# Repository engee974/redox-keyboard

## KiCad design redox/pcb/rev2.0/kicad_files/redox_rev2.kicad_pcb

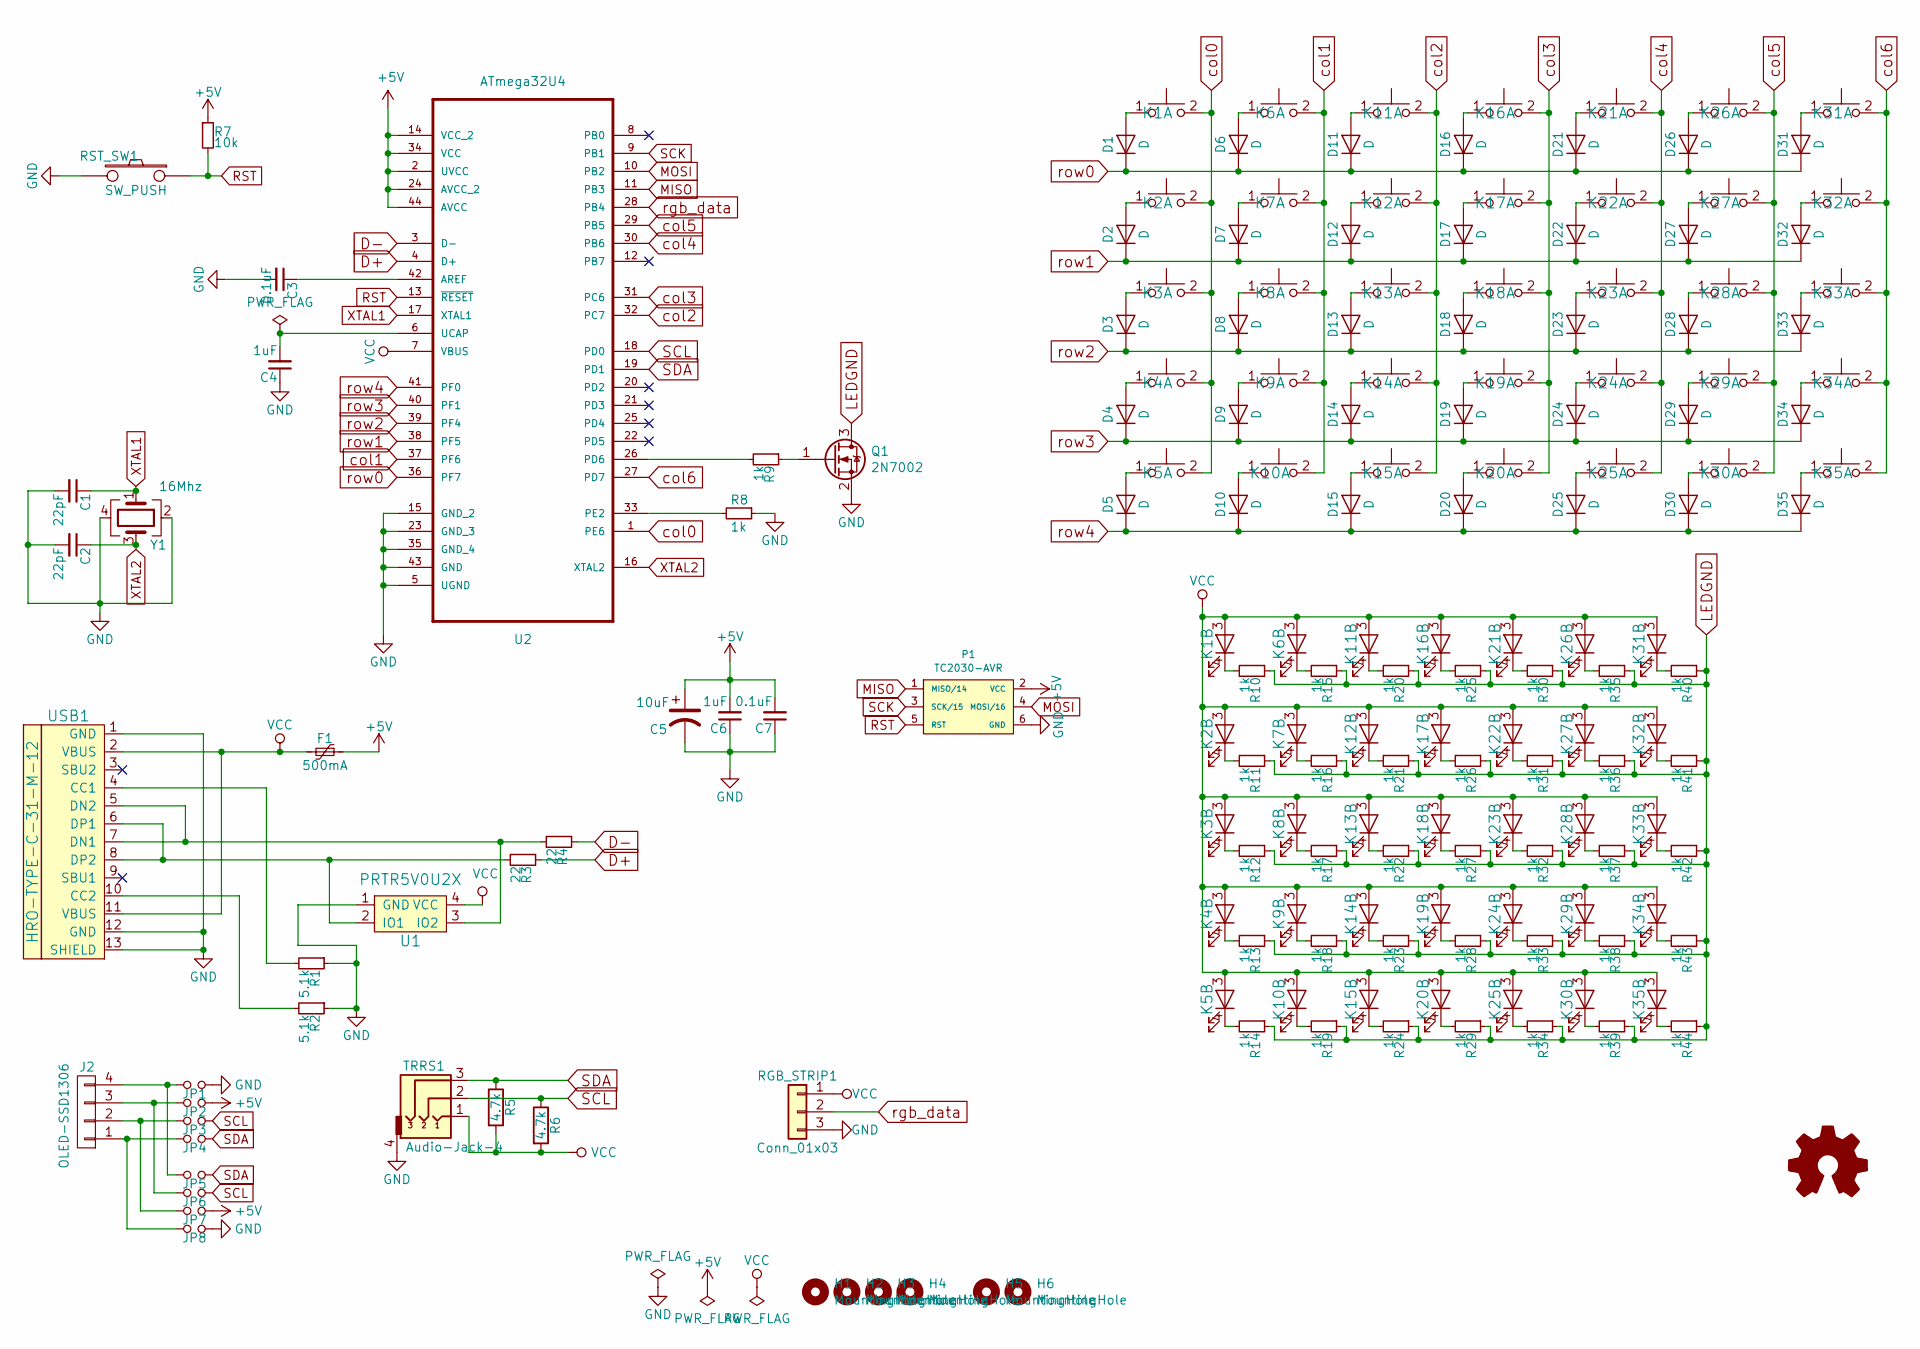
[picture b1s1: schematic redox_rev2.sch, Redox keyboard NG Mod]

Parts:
C1, C2: 22pF; C_0603
C3, C7: 0.1uF; C_0603
C4, C6: 1uF; C_0603
C5: 10uF; CP_EIA-3216-12_Kemet-S_Pad1.58x1.35mm_HandSolder
D1, D2, D3, D4, D5, D6, D7, D8, D9, D10, D11, D12, D13, D14, D15, D16, D17, D18, D19, D20, D21, D22, D23, D24, D25, D26, D27, D28, D29, D30, D31, D32, D33, D34, D35: D; D_0805_dualsided
F1: 500mA; Fuse_1206_3216Metric_Pad1.42x1.75mm_HandSolder
H1, H2, H3, H4: MountingHole; HOLE_M3
H5, H6: MountingHole; M2_HOLE_PCB
J2: OLED-SSD1306; OLED_4Pin
JP1, JP2, JP3, JP4, JP5, JP6, JP7, JP8: Jumper_NO_Small; Jumper
K1, K2, K3, K4, K25, K30, K32, K35: KEYSW; Mx_Alps_125-dualside_with_LED
K5, K6, K7, K8, K9, K10, K11, K12, K13, K14, K15, K16, K17, K18, K19, K20, K21, K22, K23, K24, K26, K27, K28, K29, K31, K33, K34: KEYSW; Mx_Alps_100-dualside_with_LED
P1: TC2030-AVR; PinHeader_2x03_P2.54mm_Vertical
Q1: 2N7002; SOT-23
R1, R2: 5.1k; R_0603
R3, R4: 22; R_0603
R5, R6: 4.7k; Resistor-Compact
R7: 10k; R_0603
R8, R9: 1k; R_0603
R10, R11, R12, R13, R14, R15, R16, R17, R18, R19, R20, R21, R22, R23, R24, R25, R26, R27, R28, R29, R30, R31, R32, R33, R34, R35, R36, R37, R38, R39, R40, R41, R42, R43, R44: 1k; R_0805_dualsided
RGB_STRIP1: Conn_01x03; PinHeader_1x03_P2.54mm_Vertical
RST_SW1: SW_PUSH; TACT_SWITCH_TVBP06
TRRS1: Audio-Jack-4; TRRS-PJ-320A-dual
U1: PRTR5V0U2X; SOT143B
U2: ATmega32U4; QFN-44-1EP_7x7mm_P0.5mm_EP5.2x5.2mm_ThermalVias
USB1: HRO-TYPE-C-31-M-12; HRO-TYPE-C-31-M-12-Assembly_dualsided
Y1: 16Mhz; Crystal_SMD_3225-4Pin_3.2x2.5mm

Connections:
+5V: C5.1, C6.2, C7.2, F1.1, JP2.2, JP7.2, P1.2 (VCC), R7.1, U2.2 (UVCC), U2.14 (VCC_2), U2.24 (AVCC_2), U2.34 (VCC), U2.44 (AVCC)
D+: R3.1, U2.4 (D+)
D-: R4.1, U2.3 (D-)
GND: C1.2, C2.2, C3.2, C4.1, C5.2, C6.1, C7.1, JP1.2, JP8.2, P1.6 (GND), Q1.2 (S), R1.1, R2.1, R8.1, RGB_STRIP1.3, RST_SW1.2, TRRS1.4, U1.1 (GND), U2.5 (UGND), U2.15 (GND_2), U2.23 (GND_3), U2.35 (GND_4), U2.43 (GND), USB1.1 (GND), USB1.12 (GND), USB1.13 (SHIELD), Y1.2, Y1.4
LEDGND: Q1.3 (D), R10.1, R11.1, R12.1, R13.1, R14.1, R15.1, R16.1, R17.1, R18.1, R19.1, R20.1, R21.1, R22.1, R23.1, R24.1, R25.1, R26.1, R27.1, R28.1, R29.1, R30.1, R31.1, R32.1, R33.1, R34.1, R35.1, R36.1, R37.1, R38.1, R39.1, R40.1, R41.1, R42.1, R43.1, R44.1
MISO: P1.1 (MISO/14), U2.11 (PB3)
MOSI: P1.4 (MOSI/16), U2.10 (PB2)
unnamed: C3.1, U2.42 (AREF)
unnamed: C4.2, U2.6 (UCAP)
unnamed: D1.2 (A), K1.1
unnamed: D2.2 (A), K2.1
unnamed: D3.2 (A), K3.1
unnamed: D4.2 (A), K4.1
unnamed: D5.2 (A), K5.1
unnamed: D6.2 (A), K6.1
unnamed: D7.2 (A), K7.1
unnamed: D8.2 (A), K8.1
unnamed: D9.2 (A), K9.1
unnamed: D10.2 (A), K10.1
unnamed: D11.2 (A), K11.1
unnamed: D12.2 (A), K12.1
unnamed: D13.2 (A), K13.1
unnamed: D14.2 (A), K14.1
unnamed: D15.2 (A), K15.1
unnamed: D16.2 (A), K16.1
unnamed: D17.2 (A), K17.1
unnamed: D18.2 (A), K18.1
unnamed: D19.2 (A), K19.1
unnamed: D20.2 (A), K20.1
unnamed: D21.2 (A), K21.1
unnamed: D22.2 (A), K22.1
unnamed: D23.2 (A), K23.1
unnamed: D24.2 (A), K24.1
unnamed: D25.2 (A), K25.1
unnamed: D26.2 (A), K26.1
unnamed: D27.2 (A), K27.1
unnamed: D28.2 (A), K28.1
unnamed: D29.2 (A), K29.1
unnamed: D30.2 (A), K30.1
unnamed: D31.2 (A), K31.1
unnamed: D32.2 (A), K32.1
unnamed: D33.2 (A), K33.1
unnamed: D34.2 (A), K34.1
unnamed: D35.2 (A), K35.1
unnamed: J2.1, JP4.1, JP8.1
unnamed: J2.2, JP3.1, JP7.1
unnamed: J2.3, JP2.1, JP6.1
unnamed: J2.4, JP1.1, JP5.1
unnamed: K1.4, R10.2
unnamed: K2.4, R11.2
unnamed: K3.4, R12.2
unnamed: K4.4, R13.2
unnamed: K5.4, R14.2
unnamed: K6.4, R15.2
unnamed: K7.4, R16.2
unnamed: K8.4, R17.2
unnamed: K9.4, R18.2
unnamed: K10.4, R19.2
unnamed: K11.4, R20.2
unnamed: K12.4, R21.2
unnamed: K13.4, R22.2
unnamed: K14.4, R23.2
unnamed: K15.4, R24.2
unnamed: K16.4, R25.2
unnamed: K17.4, R26.2
unnamed: K18.4, R27.2
unnamed: K19.4, R28.2
unnamed: K20.4, R29.2
unnamed: K21.4, R30.2
unnamed: K22.4, R31.2
unnamed: K23.4, R32.2
unnamed: K24.4, R33.2
unnamed: K25.4, R34.2
unnamed: K26.4, R35.2
unnamed: K27.4, R36.2
unnamed: K28.4, R37.2
unnamed: K29.4, R38.2
unnamed: K30.4, R39.2
unnamed: K31.4, R40.2
unnamed: K32.4, R41.2
unnamed: K33.4, R42.2
unnamed: K34.4, R43.2
unnamed: K35.4, R44.2
unnamed: Q1.1 (G), R9.1
unnamed: R1.2, USB1.4 (CC1)
unnamed: R2.2, USB1.10 (CC2)
unnamed: R3.2, U1.2 (IO1), USB1.6 (DP1), USB1.8 (DP2)
unnamed: R4.2, U1.3 (IO2), USB1.5 (DN2), USB1.7 (DN1)
unnamed: R8.2, U2.33 (PE2)
unnamed: R9.2, U2.26 (PD6)
RST: P1.5 (RST), R7.2, RST_SW1.1, U2.13 (~RESET)
SCK: P1.3 (SCK/15), U2.9 (PB1)
SCL: JP3.2, JP6.2, R6.1, TRRS1.2, U2.18 (PD0)
SDA: JP4.2, JP5.2, R5.1, TRRS1.3, U2.19 (PD1)
VCC: F1.2, K1.3, K2.3, K3.3, K4.3, K5.3, K6.3, K7.3, K8.3, K9.3, K10.3, K11.3, K12.3, K13.3, K14.3, K15.3, K16.3, K17.3, K18.3, K19.3, K20.3, K21.3, K22.3, K23.3, K24.3, K25.3, K26.3, K27.3, K28.3, K29.3, K30.3, K31.3, K32.3, K33.3, K34.3, K35.3, R5.2, R6.2, RGB_STRIP1.1, TRRS1.1, U1.4 (VCC), U2.7 (VBUS), USB1.2 (VBUS), USB1.11 (VBUS)
XTAL1: C1.1, U2.17 (XTAL1), Y1.1
XTAL2: C2.1, U2.16 (XTAL2), Y1.3
col0: K1.2, K2.2, K3.2, K4.2, K5.2, U2.1 (PE6)
col1: K6.2, K7.2, K8.2, K9.2, K10.2, U2.37 (PF6)
col2: K11.2, K12.2, K13.2, K14.2, K15.2, U2.32 (PC7)
col3: K16.2, K17.2, K18.2, K19.2, K20.2, U2.31 (PC6)
col4: K21.2, K22.2, K23.2, K24.2, K25.2, U2.30 (PB6)
col5: K26.2, K27.2, K28.2, K29.2, K30.2, U2.29 (PB5)
col6: K31.2, K32.2, K33.2, K34.2, K35.2, U2.27 (PD7)
rgb_data: RGB_STRIP1.2, U2.28 (PB4)
row0: D1.1 (K), D6.1 (K), D11.1 (K), D16.1 (K), D21.1 (K), D26.1 (K), D31.1 (K), U2.36 (PF7)
row1: D2.1 (K), D7.1 (K), D12.1 (K), D17.1 (K), D22.1 (K), D27.1 (K), D32.1 (K), U2.38 (PF5)
row2: D3.1 (K), D8.1 (K), D13.1 (K), D18.1 (K), D23.1 (K), D28.1 (K), D33.1 (K), U2.39 (PF4)
row3: D4.1 (K), D9.1 (K), D14.1 (K), D19.1 (K), D24.1 (K), D29.1 (K), D34.1 (K), U2.40 (PF1)
row4: D5.1 (K), D10.1 (K), D15.1 (K), D20.1 (K), D25.1 (K), D30.1 (K), D35.1 (K), U2.41 (PF0)

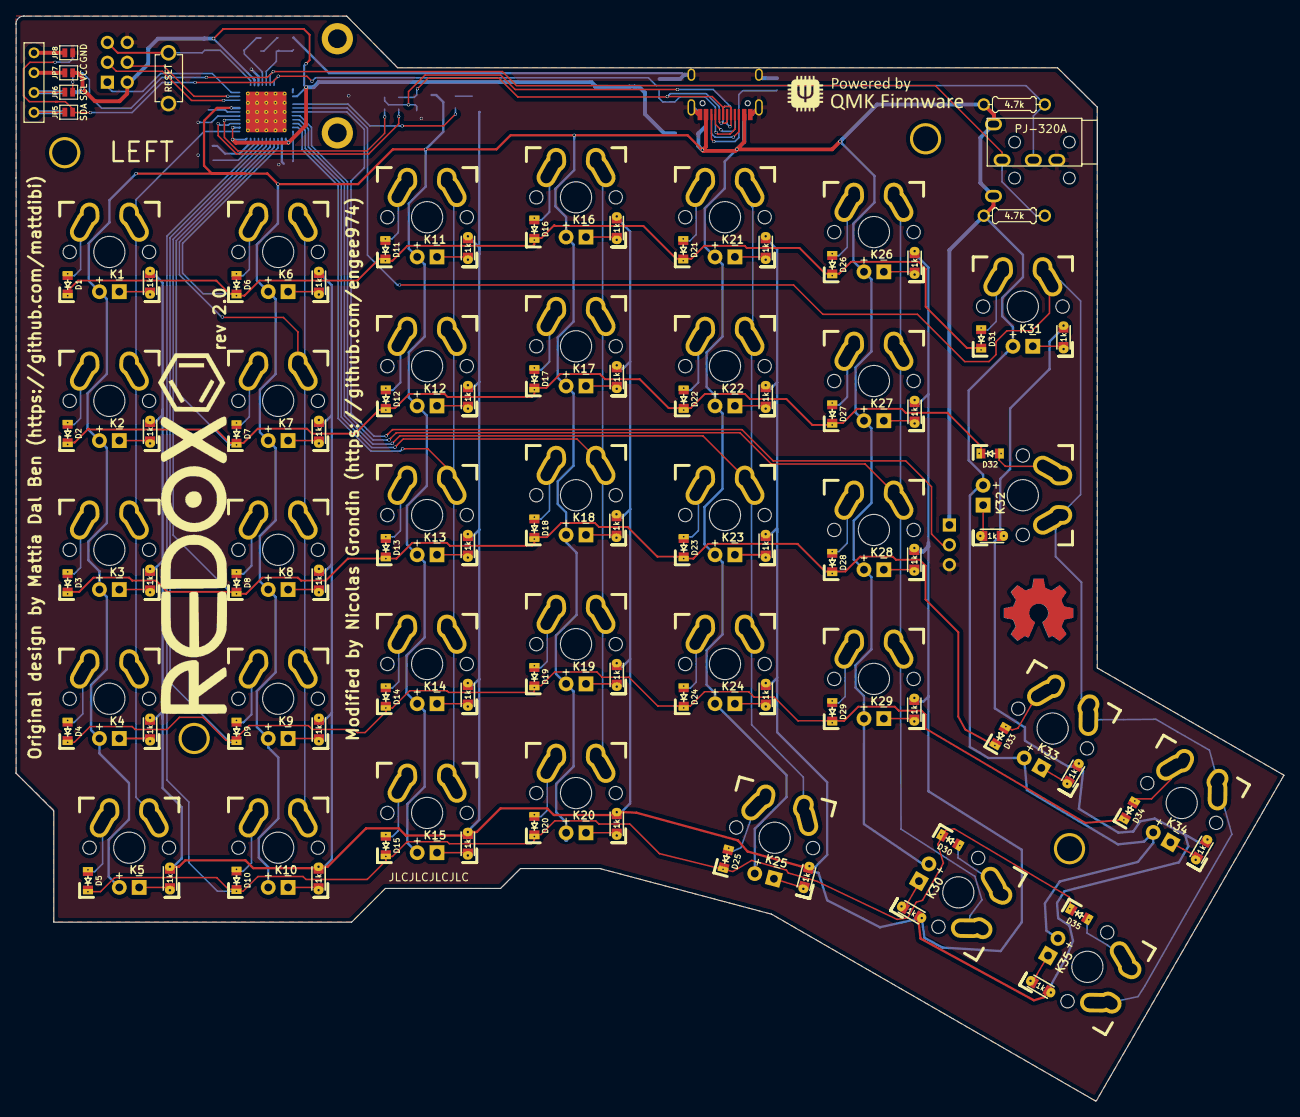
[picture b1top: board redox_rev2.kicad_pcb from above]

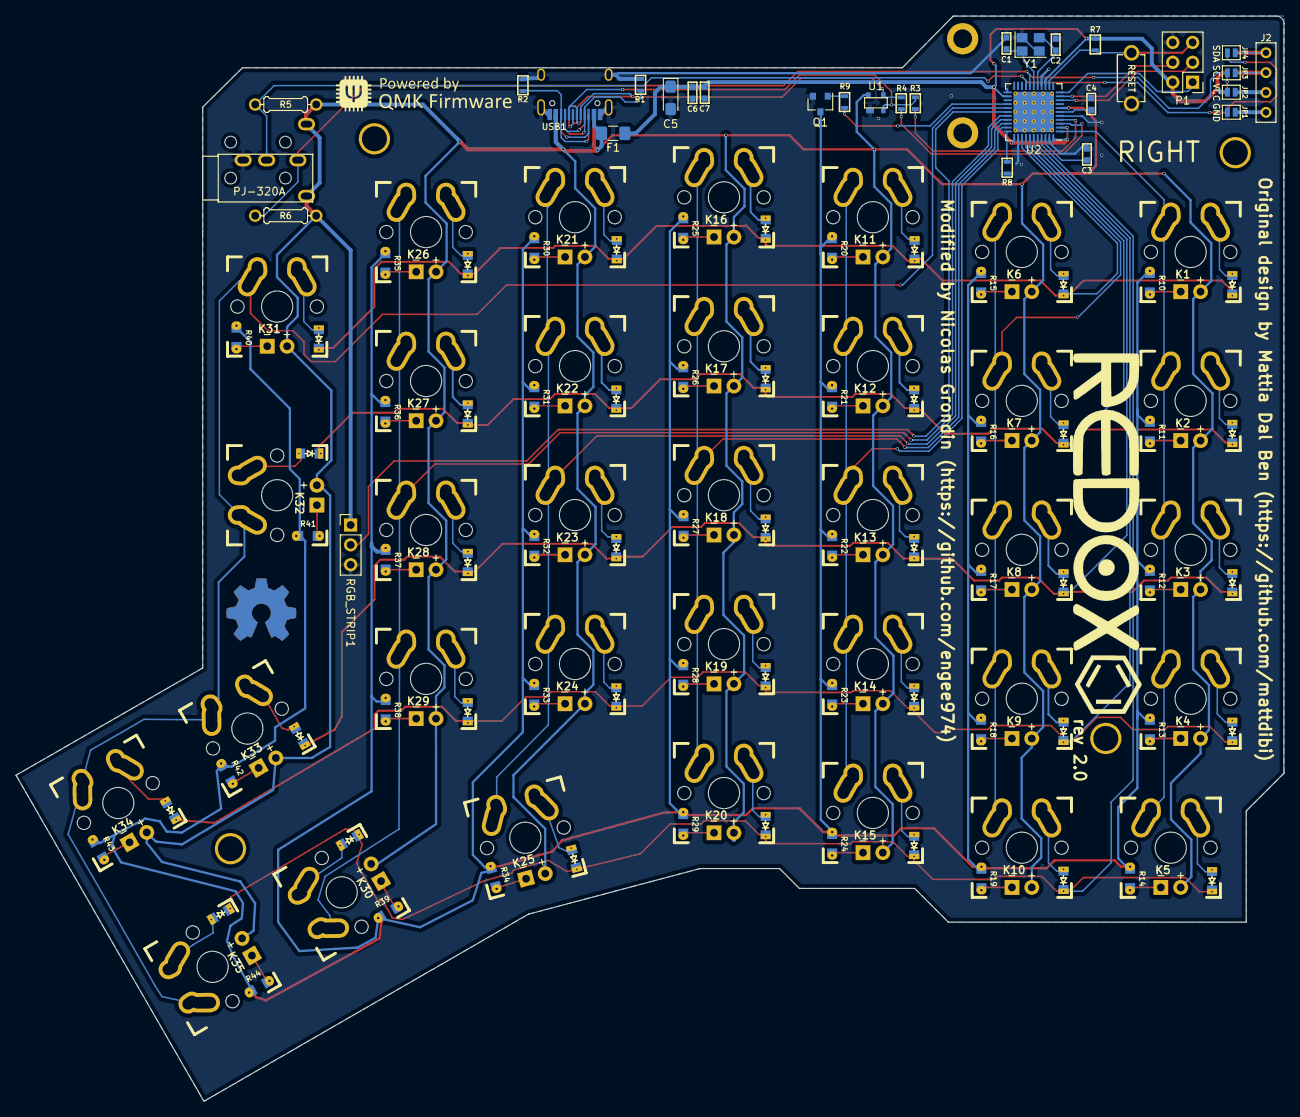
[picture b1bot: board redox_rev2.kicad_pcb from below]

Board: 2 copper layers, 162.2 x 138.8 mm, 150 parts (29 on the bottom side), 110 nets.

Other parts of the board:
QMK_BOTTOM: LOGO; qmk-badge
QMK_FRONT: LOGO; qmk-badge
REDOX_BOTTOM: LOGO; redox-logo
REDOX_FRONT: LOGO; redox-logo

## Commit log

2020-05-08 Initiating My personal rev2.0
2020-05-08 PCB Routing in progress
2020-05-09 Create dual sided usb
2020-05-09 Routing almost finished
2020-05-09 PCB finished for rev2.0
2020-05-09 Add OSH logo
2020-05-09 try to add themal viad for the ATMEGA32u4-MU
2020-05-09 Change ATùega32u4-MU QFN-44 footprint from standard library
2020-05-10 PCB - Add OSHW copper logo
2020-05-10 Add holes for OLED cover and moove mounting holes
2020-05-11 Create Case from pcb
2020-05-11 Remove kicad-ATmega32u4 submodule
2020-05-11 Move mounting holes to be compliant with redox rev1
2020-05-12 Schematic correction : replace VCC by VBUS and +5V by VCC, some other minor changes
2020-05-12 Remove submodules
2020-05-12 remove correctly submodules
2020-05-12 re add submodules
2020-05-12 Case for redox Rev2 NG
2020-05-13 Replace the reset switch footprint by something easier to find - 6x6 push button
2020-05-13 create 2 version of the PCB : SMD (the original ref2.0_ng) and THT to use with an arduino Pro Micro
2020-05-14 Change PCB holes placement, TRSS connector, add JLC id.
